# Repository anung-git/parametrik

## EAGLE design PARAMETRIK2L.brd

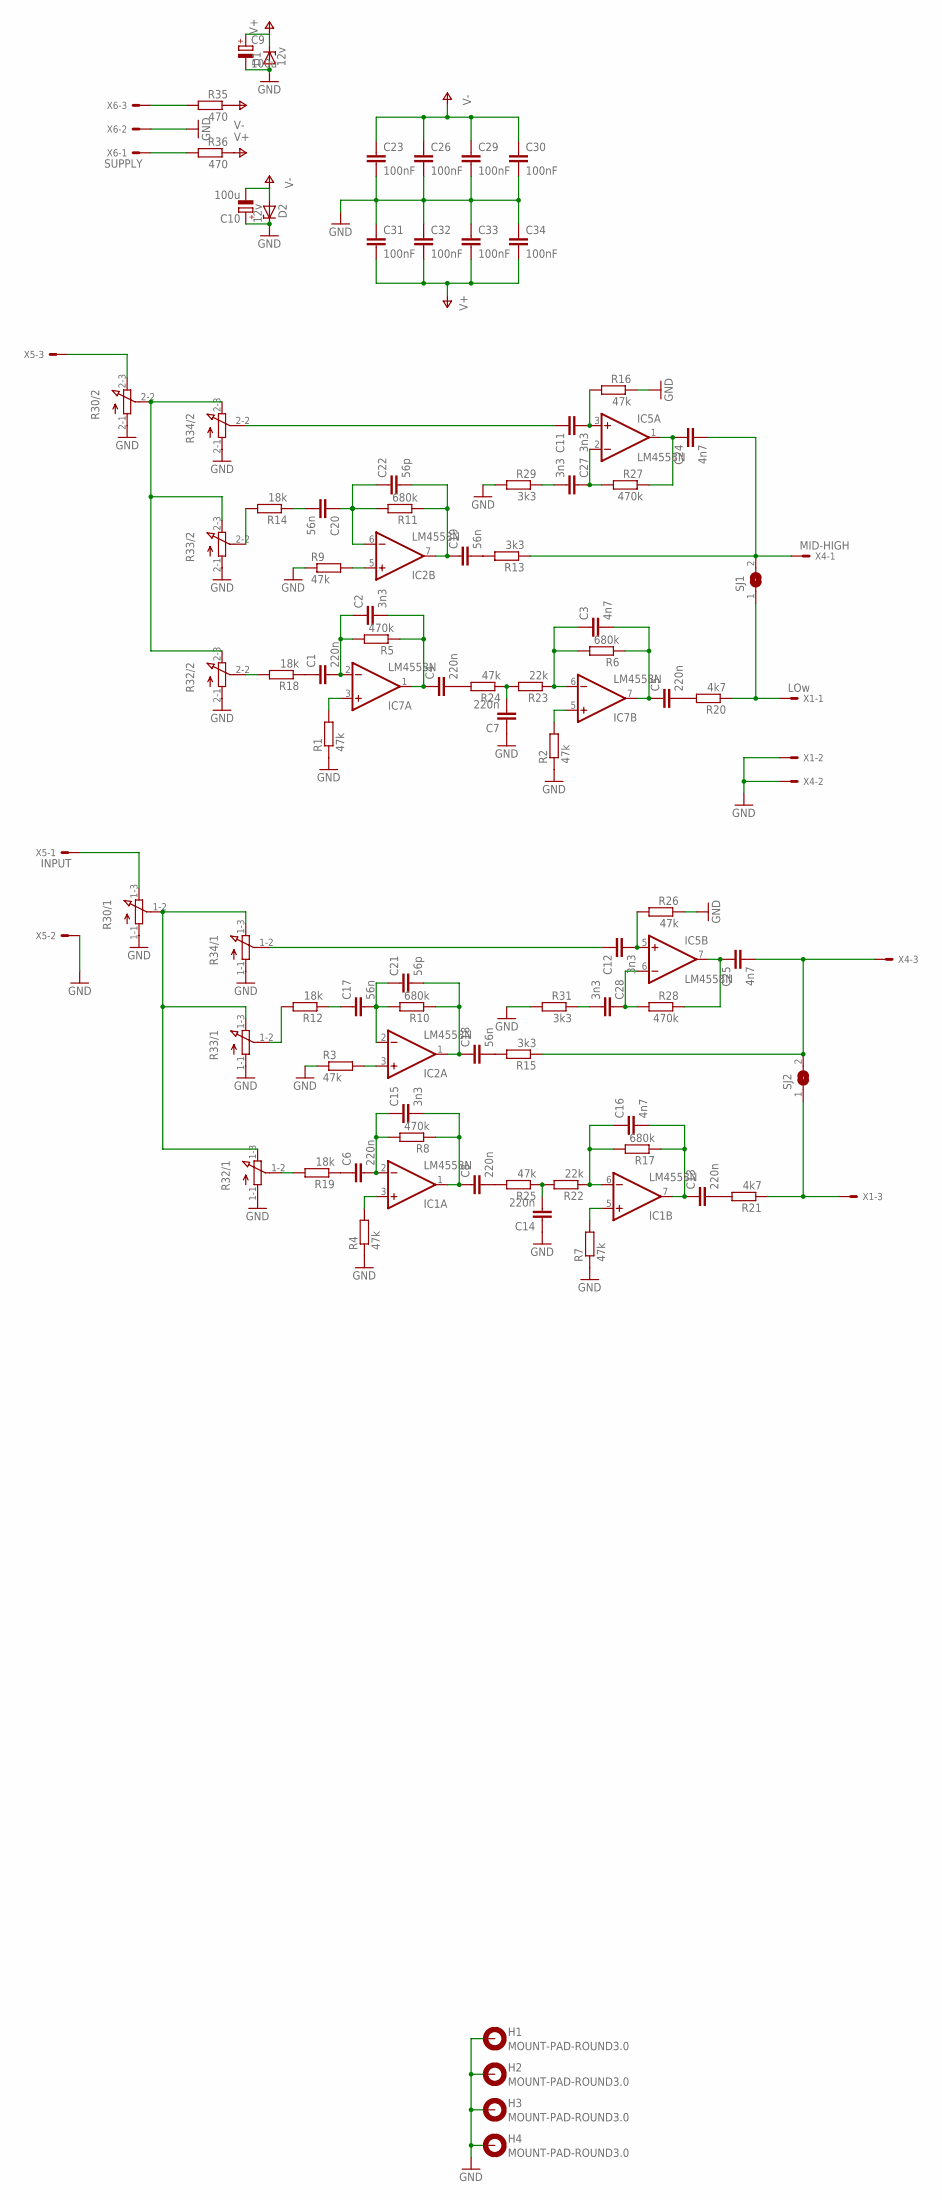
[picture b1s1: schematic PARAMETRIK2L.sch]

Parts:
C1, C4, C5, C6, C7, C8, C13, C14: 220n; C050-030X075
C2, C11, C12, C15, C27, C28: 3n3; C025-024X044
C3, C16, C24, C25: 4n7; C025-024X044
C9, C10: 100u; E2,5-6
C17, C18, C19, C20: 56n; C050-030X075
C21, C22: 56p; C025-024X044
C23, C26, C29, C30, C31, C32, C33, C34: 100nF; C050-024X044
D1, D2: 12v; DO35Z10
H1, H2, H3, H4: MOUNT-PAD-ROUND3.0; 3,0-PAD
IC1, IC2, IC5, IC7: LM4558N; DIL08
R1, R2, R3, R4, R7, R9, R16, R24, R25, R26: 47k; 0207/2V
R5, R8, R27, R28: 470k; 0207/2V
R6, R10, R11, R17: 680k; 0207/2V
R12, R14, R18, R19: 18k; 0207/2V
R13, R15, R29, R31: 3k3; 0207/2V
R20, R21: 4k7; 0207/2V
R22, R23: 22k; 0207/2V
R30, R32, R33, R34: 3RP/1610G
R35, R36: 470; 0207/10
SJ1, SJ2: SJ
X1: LOw; 22-23-2031
X4: MID-HIGH; 22-23-2031
X5: INPUT; 22-23-2031
X6: SUPPLY; 22-23-2031

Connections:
GND: C7.1, C9.-, C10.+, C14.1, C23.2, C26.2, C29.2, C30.2, C31.1, C32.1, C33.1, C34.1, D1.A, D2.C, H1.B3,0, H2.B3,0, H3.B3,0, H4.B3,0, R1.1, R2.1, R3.1, R4.1, R7.1, R9.1, R16.1, R26.1, R29.2, R30.1-1 (A), R30.2-1 (A), R31.2, R32.1-1 (A), R32.2-1 (A), R33.1-1 (A), R33.2-1 (A), R34.1-1 (A), R34.2-1 (A), X1.2, X4.2, X5.2, X6.2
unnamed: IC1.3 (+IN), R4.2
unnamed: IC1.5 (+IN), R7.2
unnamed: IC7.3 (+IN), R1.2
unnamed: IC7.5 (+IN), R2.2
unnamed: C1.2, C2.1, IC7.2 (-IN), R5.2
unnamed: C6.2, C15.1, IC1.2 (-IN), R8.2
unnamed: C8.1, C15.2, IC1.1 (OUT), R8.1
unnamed: C16.1, IC1.6 (-IN), R17.2, R22.1
unnamed: C13.1, C16.2, IC1.7 (OUT), R17.1
unnamed: C2.2, C4.1, IC7.1 (OUT), R5.1
unnamed: C3.1, IC7.6 (-IN), R6.2, R23.1
unnamed: C3.2, C5.1, IC7.7 (OUT), R6.1
unnamed: IC2.3 (+IN), R3.2
unnamed: IC2.5 (+IN), R9.2
unnamed: C17.2, C21.1, IC2.2 (-IN), R10.2
unnamed: C18.1, C21.2, IC2.1 (OUT), R10.1
unnamed: C20.1, C22.1, IC2.6 (-IN), R11.2
unnamed: C19.1, C22.2, IC2.7 (OUT), R11.1
unnamed: C17.1, R12.1
unnamed: C19.2, R13.2
unnamed: C18.2, R15.2
unnamed: C28.2, R31.1
unnamed: C20.2, R14.1
unnamed: R12.2, R33.1-2 (S)
unnamed: C6.1, R19.1
unnamed: C1.1, R18.1
unnamed: C13.2, R21.2
unnamed: C5.2, R20.2
unnamed: C24.2, R13.1, SJ1.2, X4.1
unnamed: C11.2, IC5.3 (+IN), R16.2
unnamed: C8.2, R25.2
unnamed: C14.2, R22.2, R25.1
unnamed: C4.2, R24.2
unnamed: C7.2, R23.2, R24.1
unnamed: C12.2, IC5.5 (+IN), R26.2
unnamed: C27.1, IC5.2 (-IN), R27.2
unnamed: C24.1, IC5.1 (OUT), R27.1
unnamed: C28.1, IC5.6 (-IN), R28.2
unnamed: C25.1, IC5.7 (OUT), R28.1
unnamed: C27.2, R29.1
unnamed: C25.2, R15.1, SJ2.2, X4.3
unnamed: R14.2, R33.2-2 (S)
unnamed: R19.2, R32.1-2 (S)
unnamed: R18.2, R32.2-2 (S)
unnamed: R30.2-2 (S), R32.2-3 (E), R33.2-3 (E), R34.2-3 (E)
unnamed: R35.2, X6.3
unnamed: R30.1-2 (S), R32.1-3 (E), R33.1-3 (E), R34.1-3 (E)
unnamed: R36.2, X6.1
unnamed: R30.1-3 (E), X5.1
unnamed: R30.2-3 (E), X5.3
unnamed: C11.1, R34.2-2 (S)
unnamed: C12.1, R34.1-2 (S)
unnamed: R21.1, SJ2.1, X1.3
unnamed: R20.1, SJ1.1, X1.1
V+: C9.+, C31.2, C32.2, C33.2, C34.2, D1.C, IC1.8 (V+), IC2.8 (V+), IC5.8 (V+), IC7.8 (V+), R36.1
V-: C10.-, C23.1, C26.1, C29.1, C30.1, D2.A, IC1.4 (V-), IC2.4 (V-), IC5.4 (V-), IC7.4 (V-), R35.1

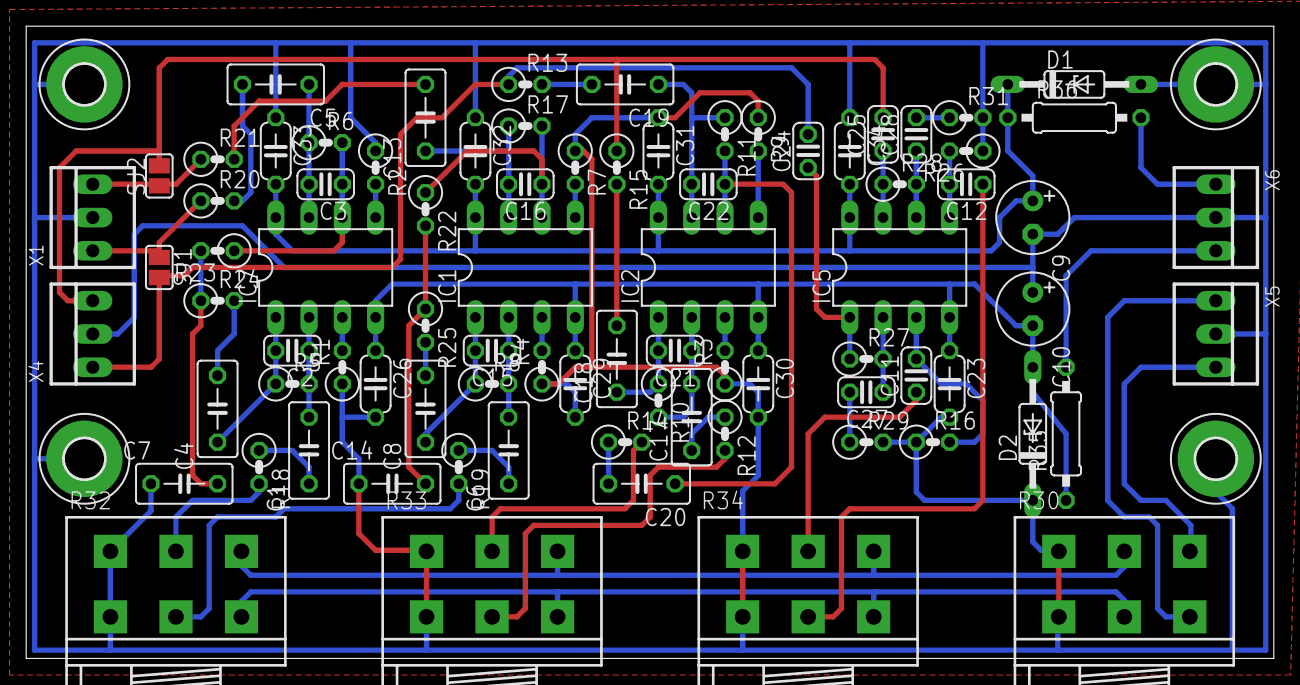
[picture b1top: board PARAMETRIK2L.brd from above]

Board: 2 copper layers, 95.2 x 48.3 mm, 86 parts (0 on the bottom side), 57 nets.

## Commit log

2019-06-04 tambah file eagle parametrik
2021-01-20 double layer
